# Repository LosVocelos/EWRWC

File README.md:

# EWRWC
Educational wheeled robot with camera

## Sources

These are the components (and their 3D models) I'm using in this project:

### Modules

| Part | Component | Store page | 3D model |
| ---------- | ---------- | ---------- | ---------- |
| EWRWC Add-on | Custom PCB (described below) | *None yet* | [Pi_zero_header.step](PCB/Pi_zero_header.step)
| Brain (CPU) | Raspberry pi zero 2 w | [RPishop - Zero 2 w](https://rpishop.cz/zero/4311-raspberry-pi-zero-2-w-5056561800004.html) | [GrabCAD - Zero 2 w](https://grabcad.com/library/raspberry-pi-zero-2-w-1) |
| Camera | Raspberry Pi camera V2 | [RPishop - camera v2](https://rpishop.cz/mipi-kamerove-moduly/329-raspberry-pi-kamera-modul-v2.html) | [Thingiverse - Rpi Camera v2.1](https://www.thingiverse.com/thing:2376448/files) |
| Camera cable (200 mm) | Camera Cable Standard - Mini | [RPishop - camera cable](https://rpishop.cz/mipi-kamerove-moduly/329-raspberry-pi-kamera-modul-v2.html) |  |
| 2x DC motor | 2x GA12-N20 3V 500RPM | [Techfun - motor 3V 500RPM](https://techfun.sk/produkt/dc-motorcek-s-prevodom-rozne-typy/?attribute_pa_motor=3v-500rpm) | [GrabCAD - N20 Gearmotor](https://grabcad.com/library/dc-micro-metal-gearmotor-1) |
| Ball (support point) | Rotating ball 3PI N20 | [Techfun - 3PI N20](https://techfun.sk/produkt/gulicka-n20-pre-stavebnice-robotickych-auticok/) |  |
| Battery holder | 18650 Li-Ion Holder | [LaskaKit - 18650 Holder](https://www.laskakit.cz/bateriovy-box-1x18650-dratove-vyvody/) | [GrabCAD - 18650 Holder](https://grabcad.com/library/18650-battery-holder-generic-1) |
| Battery | 18650 Li-Ion 2800mAh 10A | [Techfun - INR18650-28HE](https://techfun.sk/produkt/18650-bateria-tenpower-inr18650-28he-2800mah-10a/) |  |

*These components are optional, but I have examples for them:*

| Part | Component | Store page | 3D model |
| ---------- | ---------- | ---------- | ---------- |
| 3 axis Magnetometer | I2C HMC5883l | [LaskaKit - HMC5883l](https://www.laskakit.cz/3-osy-magnetometr-a-kompas-hmc5883l/) |  |
| Laser distance sensor | I2C VL53L0X | [LaskaKit - VL53L0X](https://www.laskakit.cz/laserovy-senzor-vzdalenosti-gy-vl53l0x-i2c/) |  |
| Module of light intensity | I2C GY-302 BH1750 | [RPishop - GY-302](https://rpishop.cz/svetlo/2435-modul-intenzity-svetla-gy-302-bh1750.html) |  |

*These components are optional, but I don't use them:*

| Part | Component | Store page | 3D model |
| ---------- | ---------- | ---------- | ---------- |
| Light intensity sensor | I2C VELM7700 | [LaskaKit - VELM7700](https://www.laskakit.cz/snimac-intenzity-osvetleni-veml7700--i2c/) |  |
| Temp + humidity sensor | I2C SHT30 | [LaskaKit - SHT30](https://www.laskakit.cz/senzor-teploty-a-vlhkosti-vzduchu-sht30/) |  |
| Blue + Yellow OLED | SPI OLED 128x64 | [LaskaKit - OLED 0.96"](https://www.laskakit.cz/oled-displej-modry-a-zluty-128x64-0-96--spi/) |  |
| Blue + Yellow OLED | I2C OLED 128x64 | [LaskaKit - OLED 0.96"](https://www.laskakit.cz/oled-displej-modry-a-zluty-128x64-0-96--i2c/) |  |

### PCB (EWRWC Add-on)

I previously called the board a Pi-Zero-Header (that's why the files are called that way).
But that name didn't grasp the functionality well, so I decided to call it EWRWC Add-on (I wanted to call it the HAT, but by board doesn't meet all requirements to be called that way).

List of parts used in the Add-on board:

| Part | Manufacturer | Component | Store page | Documentation |
| ---------- | ---------- | ---------- | ---------- | ---------- |
| Microcontroller | Raspberry Pi | RP2040 | [LCSC - RP2040](https://www.lcsc.com/product-detail/Microcontroller-Units-MCUs-MPUs-SOCs_Raspberry-Pi-RP2040_C2040.html) | [rp2040-datasheet.pdf](https://datasheets.raspberrypi.com/rp2040/rp2040-datasheet.pdf) |
| MCU Flash memory | Winbond | Q25W128JV | [JLCPCB - Q25W128JVSIQ](https://jlcpcb.com/partdetail/WinbondElec-W25Q128JVSIQ/C97521) | [W25Q128JV.pdf](https://www.winbond.com/resource-files/W25Q128JV%20RevI%2008232021%20Plus.pdf) |
| MCU Crystal | YXC | X322512MSB4SI | [JLCPCB - X322512MSB4SI](https://jlcpcb.com/partdetail/Yxc-X322512MSB4SI/C9002) | [YSX321SL.pdf](https://image.seapx.com/mall/yangxin/3/20231030/YSX321SL-687795.pdf) |
| Battery management | Texas Instruments | BQ25792 | [LCSC - BQ25792](https://www.lcsc.com/product-detail/Battery-Management-ICs_Texas-Instruments-BQ25792RQMR_C2862876.html) | [bq25792.pdf](https://www.ti.com/lit/ds/symlink/bq25792.pdf) |
| 5V / 3V3 Regulator | Texas Instruments | TPS63070 | [LCSC - TPS63070](https://www.lcsc.com/product-detail/DC-DC-Converters_Texas-Instruments-TPS63070RNMR_C109322.html) | [tps63070.pdf](https://www.ti.com/lit/ds/symlink/tps63070.pdf) |
| 5V / 3V3 Regulator | Chilisin Elec | BMRA000404201R0MA1 | [LCSC - BMRA000404201R0](https://www.lcsc.com/product-detail/Power-Inductors_Chilisin-Elec-BMRA000404201R0MA1_C2838337.html) | [BMRx_Series.pdf](https://www.chilisin.com/upload/media/product/power/file/BMRx_Series.pdf) |
| Motor Driver (2 H) | Toshiba | TB6612FNG | [LCSC - TB6612FNG](https://www.lcsc.com/product-detail/Motor-Driver-ICs_TOSHIBA-TB6612FNG-O-C-8-EL_C88224.html) | [TB6612FNG.pdf](https://toshiba.semicon-storage.com/info/TB6612FNG_datasheet_en_20141001.pdf?did=10660&prodName=TB6612FNG) |

There are much more parts used in this project (inductors, buttons, connectors, LEDs and a bunch of capacitors and resistors), but only those in the table are crucialfor the functionality and choosing the rest of the parts.

--------------------------------------------------

TODO:

- [x] Gather all sources
- [x] Design the main PCB
- [x] Complete the PCB
- [x] Design chassis
- [x] Print and ready the chassis
- [x] Complete the hardware
- [x] Write the software
- [x] Write the framework
- [x] Add some use for the camera
- [x] Write documentation
- [ ] Finalize
- [ ] Play with it :)

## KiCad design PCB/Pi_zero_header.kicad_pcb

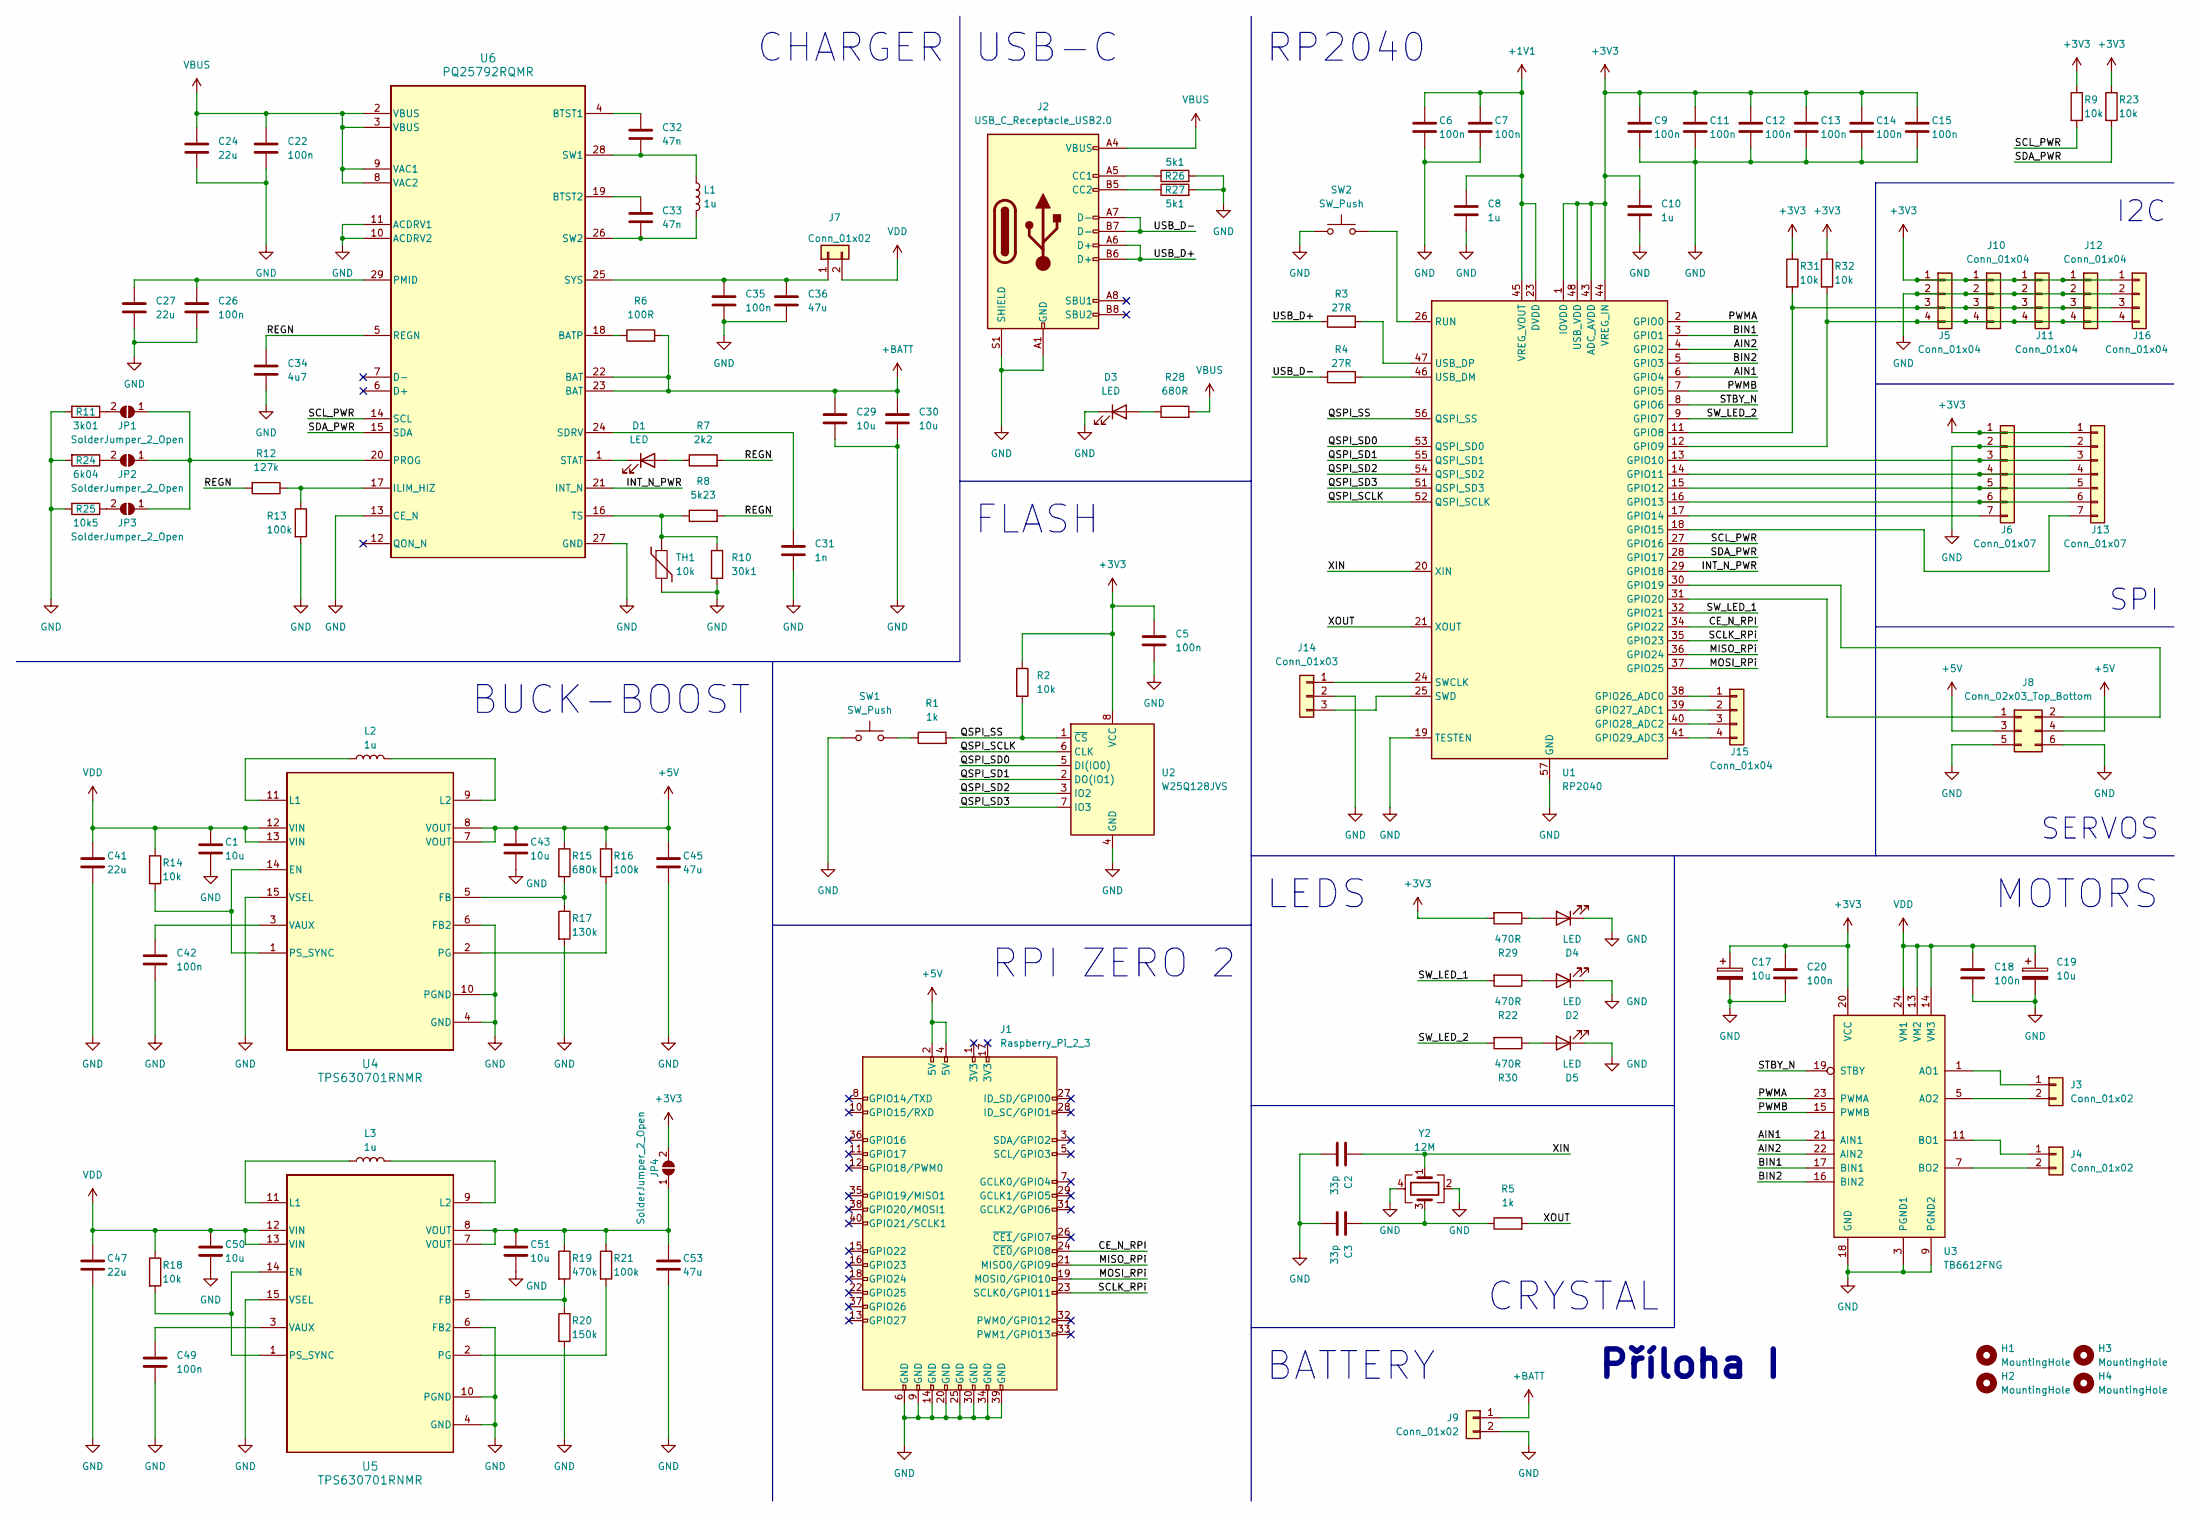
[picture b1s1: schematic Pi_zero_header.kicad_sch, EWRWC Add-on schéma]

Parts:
C1, C43, C50, C51: 10u; C_0603_1608Metric; LCSC C96446
C2, C3: 33p; C_0402_1005Metric; LCSC C1562
C5, C6, C7, C9, C11, C12, C13, C14, C15: 100n; C_0402_1005Metric; LCSC C1525
C8, C10: 1u; C_0402_1005Metric; LCSC C52923
C17, C19: 10u; CP_EIA-3216-18_Kemet-A; LCSC C7171
C18, C20, C22, C26, C35, C42, C49: 100n; C_0402_1005Metric; LCSC C307331
C24, C27, C41, C47: 22u; C_0805_2012Metric; LCSC C45783
C29, C30: 10u; C_0805_2012Metric; LCSC C440198
C31: 1n; C_0402_1005Metric; LCSC C1523
C32, C33: 47n; C_0402_1005Metric; LCSC C307339
C34: 4u7; C_0603_1608Metric; LCSC C19666
C36: 47u; C_1206_3216Metric; LCSC C96123
C45, C53: 47u; C_0805_2012Metric; LCSC C16780
D1, D2: LED; LED_0603_1608Metric; LCSC C2286
D3, D4: LED; LED_0805_2012Metric; LCSC C2297
D5: LED; LED_0603_1608Metric; LCSC C72038
H1, H2, H3, H4: MountingHole; MountingHole_2.7mm
J1: Raspberry_Pi_2_3; PinSocket_2x20_P2.54mm_Vertical; LCSC C5307344
J2: USB_C_Receptacle_USB2.0; USB_C_Receptacle_HCTL_HC-TYPE-C-16P-01A; LCSC C2894897
J3, J4, J7, J9: Conn_01x02; PinHeader_1x02_P2.54mm_Vertical
J5, J10, J11, J12, J15, J16: Conn_01x04; PinHeader_1x04_P1.27mm_Vertical
J6, J13: Conn_01x07; PinHeader_1x07_P1.27mm_Vertical
J8: Conn_02x03_Top_Bottom; PinHeader_2x03_P2.54mm_Vertical
J14: Conn_01x03; PinHeader_1x03_P1.27mm_Vertical
JP1, JP2, JP3, JP4: SolderJumper_2_Open; SolderJumper-2_P1.3mm_Open_RoundedPad1.0x1.5mm
L1, L2, L3: 1u; L_Chilisin_BMRA00040420; LCSC C2838337
R1, R5: 1k; R_0402_1005Metric; LCSC C11702
R2, R9, R14, R18, R23, R31, R32: 10k; R_0402_1005Metric; LCSC C25744
R3, R4: 27R; R_0402_1005Metric; LCSC C25100
R6: 100R; R_0402_1005Metric; LCSC C25076
R7: 2k2; R_0402_1005Metric; LCSC C25879
R8: 5k23; R_0402_1005Metric; LCSC C25907
R10: 30k1; R_0402_1005Metric; LCSC C29402
R11: 3k01; R_0402_1005Metric; LCSC C25889
R12: 127k; R_0402_1005Metric; LCSC C25751
R13, R16, R21: 100k; R_0402_1005Metric; LCSC C25741
R15: 680k; R_0402_1005Metric; LCSC C4131
R17: 130k; R_0402_1005Metric; LCSC C52929
R19: 470k; R_0402_1005Metric; LCSC C25790
R20: 150k; R_0402_1005Metric; LCSC C25755
R22, R29, R30: 470R; R_0402_1005Metric; LCSC C25117
R24: 6k04; R_0402_1005Metric; LCSC C25913
R25: 10k5; R_0402_1005Metric; LCSC C25850
R26, R27: 5k1; R_0402_1005Metric; LCSC C25905
R28: 680R; R_0402_1005Metric; LCSC C25130
SW1, SW2: SW_Push; SW_SPST_PTS810; LCSC C116501
TH1: 10k; R_Axial_DIN0204_L3.6mm_D1.6mm_P2.54mm_Vertical
U1: RP2040; QFN-56-1EP_7x7mm_P0.4mm_EP3.2x3.2mm; LCSC C2040
U2: W25Q128JVS; SOIC-8_5.23x5.23mm_P1.27mm; LCSC C97521
U3: TB6612FNG; SSOP-24_5.3x8.2mm_P0.65mm; LCSC C88224
U4, U5: TPS630701RNMR; RNM0015A; LCSC C109322
U6: PQ25792RQMR; RQM0029A-MFG; LCSC C2862876
Y2: 12M; Crystal_SMD_3225-4Pin_3.2x2.5mm; LCSC C9002

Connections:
+1V1: C6.1, C7.1, C8.1, U1.23 (DVDD), U1.45 (VREG_VOUT), U1.50 (DVDD)
+3V3: C5.1, C9.1, C10.1, C11.1, C12.1, C13.1, C14.1, C15.1, C17.1, C20.1, J5.1, J6.1, J10.1, J11.1, J12.1, J13.1, J16.1, JP4.2 (B), R2.1, R9.1, R23.1, R29.2, R31.1, R32.1, U1.1 (IOVDD), U1.10 (IOVDD), U1.22 (IOVDD), U1.33 (IOVDD), U1.42 (IOVDD), U1.43 (ADC_AVDD), U1.44 (VREG_IN), U1.48 (USB_VDD), U1.49 (IOVDD), U2.8 (VCC), U3.20 (VCC)
+5V: C43.1, C45.1, J1.2 (5V), J1.4 (5V), J8.3, J8.4, R15.1, R16.1, U4.7 (VOUT), U4.8 (VOUT)
+BATT: C29.1, C30.1, J9.1, R6.2, U6.22 (BAT), U6.23 (BAT)
/AIN1: U1.6 (GPIO4), U3.21 (AIN1)
/AIN2: U1.4 (GPIO2), U3.22 (AIN2)
/BIN1: U1.3 (GPIO1), U3.17 (BIN1)
/BIN2: U1.5 (GPIO3), U3.16 (BIN2)
/CE_N_RPI: J1.24 (~CE0/GPIO8), U1.34 (GPIO22)
/INT_N_PWR: U1.29 (GPIO18), U6.21 (INT_N)
/MISO_RPi: J1.21 (MISO0/GPIO9), U1.36 (GPIO24)
/MOSI_RPi: J1.19 (MOSI0/GPIO10), U1.37 (GPIO25)
/PWMA: U1.2 (GPIO0), U3.23 (PWMA)
/PWMB: U1.7 (GPIO5), U3.15 (PWMB)
/QSPI_SCLK: U1.52 (QSPI_SCLK), U2.6 (CLK)
/QSPI_SD0: U1.53 (QSPI_SD0), U2.5 (DI(IO0))
/QSPI_SD1: U1.55 (QSPI_SD1), U2.2 (DO(IO1))
/QSPI_SD2: U1.54 (QSPI_SD2), U2.3 (IO2)
/QSPI_SD3: U1.51 (QSPI_SD3), U2.7 (IO3)
/QSPI_SS: R1.2, R2.2, U1.56 (QSPI_SS), U2.1 (~CS)
/REGN: C34.1, R7.2, R8.2, R12.2, U6.5 (REGN)
/SCLK_RPi: J1.23 (SCLK0/GPIO11), U1.35 (GPIO23)
/SCL_PWR: R9.2, U1.27 (GPIO16), U6.14 (SCL)
/SDA_PWR: R23.2, U1.28 (GPIO17), U6.15 (SDA)
/STBY_N: U1.8 (GPIO6), U3.19 (STBY)
/SW_LED_1: R22.2, U1.32 (GPIO21)
/SW_LED_2: R30.2, U1.9 (GPIO7)
/USB_D+: J2.A6 (D+), J2.B6 (D+), R3.1
/USB_D-: J2.A7 (D-), J2.B7 (D-), R4.1
/XIN: C2.1, U1.20 (XIN), Y2.1
/XOUT: R5.2, U1.21 (XOUT)
GND: C1.2, C2.2, C3.2, C5.2, C6.2, C7.2, C8.2, C9.2, C10.2, C11.2, C12.2, C13.2, C14.2, C15.2, C17.2, C18.2, C19.2, C20.2, C22.2, C24.2, C26.2, C27.2, C29.2, C30.2, C31.2, C34.2, C35.2, C36.2, C41.2, C42.2, C43.2, C45.2, C47.2, C49.2, C50.2, C51.2, C53.2, D2.1 (K), D3.1 (K), D4.1 (K), D5.1 (K), J1.6 (GND), J1.9 (GND), J1.14 (GND), J1.20 (GND), J1.25 (GND), J1.30 (GND), J1.34 (GND), J1.39 (GND), J2.A1 (GND), J2.A12 (GND), J2.B1 (GND), J2.B12 (GND), J2.S1 (SHIELD), J5.2, J6.2, J8.5, J8.6, J9.2, J10.2, J11.2, J12.2, J13.2, J14.2, J16.2, R10.2, R11.2, R13.2, R17.2, R20.2, R24.2, R25.2, R26.2, R27.2, SW1.1, SW2.1, TH1.2, U1.19 (TESTEN), U1.57 (GND), U2.4 (GND), U3.3 (PGND1), U3.4 (PGND1), U3.9 (PGND2), U3.10 (PGND2), U3.18 (GND), U4.4 (GND), U4.6 (FB2), U4.10 (PGND), U4.15 (VSEL), U5.4 (GND), U5.6 (FB2), U5.10 (PGND), U5.15 (VSEL), U6.10 (ACDRV2), U6.11 (ACDRV1), U6.13 (CE_N), U6.27 (GND), Y2.2, Y2.4
unnamed: C3.1, R5.1, Y2.3
unnamed: D1.2 (A), R7.1
unnamed: D1.1 (K), U6.1 (STAT)
unnamed: D2.2 (A), R22.1
unnamed: D3.2 (A), R28.1
unnamed: D4.2 (A), R29.1
unnamed: D5.2 (A), R30.1
unnamed: J2.A5 (CC1), R26.1
unnamed: J2.B5 (CC2), R27.1
unnamed: J3.1, U3.1 (AO1), U3.2 (AO1)
unnamed: J3.2, U3.5 (AO2), U3.6 (AO2)
unnamed: J4.1, U3.11 (BO1), U3.12 (BO1)
unnamed: J4.2, U3.7 (BO2), U3.8 (BO2)
unnamed: J6.7, U1.17 (GPIO14)
unnamed: C35.1, C36.1, J7.1, U6.25 (SYS)
unnamed: J8.1, U1.31 (GPIO20)
unnamed: J8.2, U1.30 (GPIO19)
unnamed: J5.3, J10.3, J11.3, J12.3, J16.3, R31.2, U1.11 (GPIO8)
unnamed: J5.4, J10.4, J11.4, J12.4, J16.4, R32.2, U1.12 (GPIO9)
unnamed: J6.3, J13.3, U1.13 (GPIO10)
unnamed: J6.4, J13.4, U1.14 (GPIO11)
unnamed: J6.5, J13.5, U1.15 (GPIO12)
unnamed: J6.6, J13.6, U1.16 (GPIO13)
unnamed: J13.7, U1.18 (GPIO15)
unnamed: J14.1, U1.24 (SWCLK)
unnamed: J14.3, U1.25 (SWD)
unnamed: J15.1, U1.38 (GPIO26_ADC0)
unnamed: J15.2, U1.39 (GPIO27_ADC1)
unnamed: J15.3, U1.40 (GPIO28_ADC2)
unnamed: J15.4, U1.41 (GPIO29_ADC3)
unnamed: JP1.1 (A), JP2.1 (A), JP3.1 (A), U6.20 (PROG)
unnamed: JP1.2 (B), R11.1
unnamed: JP2.2 (B), R24.1
unnamed: JP3.2 (B), R25.1
unnamed: C51.1, C53.1, JP4.1 (A), R19.1, R21.1, U5.7 (VOUT), U5.8 (VOUT)
unnamed: R1.1, SW1.2
unnamed: SW2.2, U1.26 (RUN)
unnamed: R4.2, U1.46 (USB_DM)
unnamed: R3.2, U1.47 (USB_DP)
unnamed: R14.2, U4.1 (PS_SYNC), U4.14 (EN)
unnamed: R15.2, R17.1, U4.5 (FB)
unnamed: L2.1, U4.11 (L1)
unnamed: L2.2, U4.9 (L2)
unnamed: R16.2, U4.2 (PG)
unnamed: C42.1, U4.3 (VAUX)
unnamed: R18.2, U5.1 (PS_SYNC), U5.14 (EN)
unnamed: R19.2, R20.1, U5.5 (FB)
unnamed: L3.1, U5.11 (L1)
unnamed: L3.2, U5.9 (L2)
unnamed: R21.2, U5.2 (PG)
unnamed: C49.1, U5.3 (VAUX)
unnamed: R6.1, U6.18 (BATP)
unnamed: C32.1, U6.4 (BTST1)
unnamed: C33.1, U6.19 (BTST2)
unnamed: R12.1, R13.1, U6.17 (ILIM_HIZ)
unnamed: C26.1, C27.1, U6.29 (PMID)
unnamed: C31.1, U6.24 (SDRV)
unnamed: C32.2, L1.1, U6.28 (SW1)
unnamed: C33.2, L1.2, U6.26 (SW2)
unnamed: R8.1, R10.1, TH1.1, U6.16 (TS)
VBUS: C22.1, C24.1, J2.A4 (VBUS), J2.A9 (VBUS), J2.B4 (VBUS), J2.B9 (VBUS), R28.2, U6.2 (VBUS), U6.3 (VBUS), U6.8 (VAC2), U6.9 (VAC1)
VDD: C1.1, C18.1, C19.1, C41.1, C47.1, C50.1, J7.2, R14.1, R18.1, U3.13 (VM2), U3.14 (VM3), U3.24 (VM1), U4.12 (VIN), U4.13 (VIN), U5.12 (VIN), U5.13 (VIN)

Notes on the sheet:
LEDS
RP2040
BUCK-BOOST
BATTERY
I2C
CRYSTAL
SERVOS
USB-C
RPI ZERO 2
FLASH
MOTORS
Příloha I
CHARGER
SPI

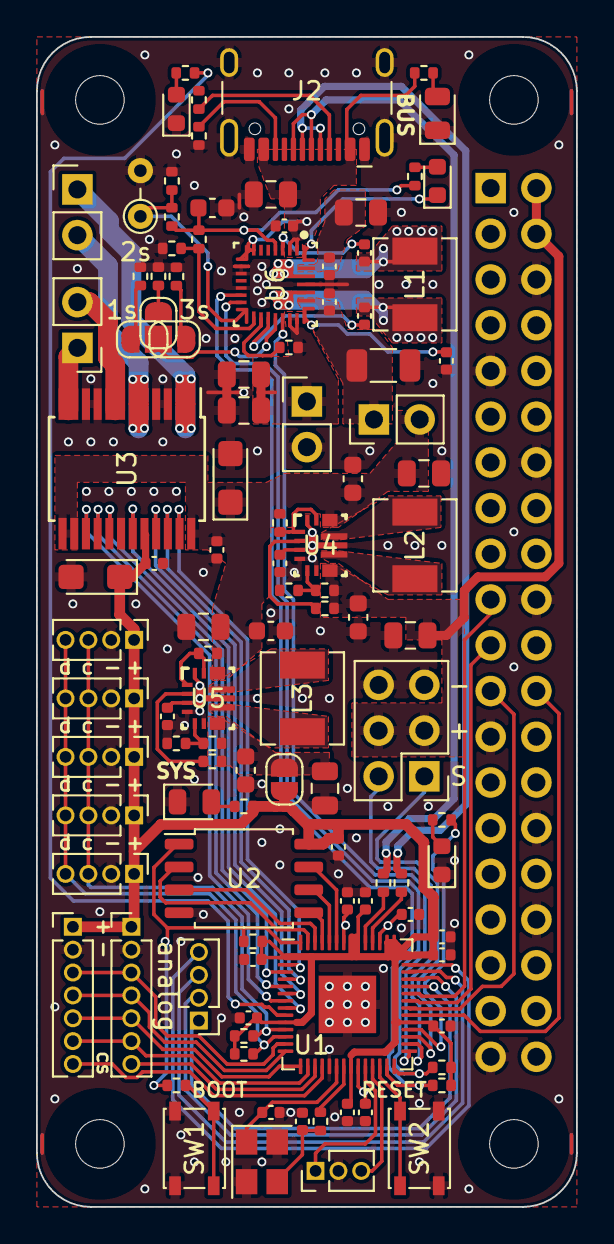
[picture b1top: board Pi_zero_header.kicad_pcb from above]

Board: 2 copper layers, 30.0 x 65.0 mm, 113 parts (1 on the bottom side), 94 nets.

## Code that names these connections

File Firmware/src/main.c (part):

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
#define STBY 6

const uint8_t motor_pins[] = {4, 2, 1, 3}; // AIN1, AIN2, BIN1, BIN2
const uint8_t pwm_pins[] = {0, 5, 19, 20}; // PWMA, PWMB, SERVOA, SERVOB

#define PWM_CLOCK_DIVIDE 25.f // Divide the PWM clock down to a more reasonable 1MHz to even be able to do 100hz but retain precision.
#define WRAP 49999.f // calculated so it matches 100hz (original frequency/desired frequency) - 1
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
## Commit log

2023-12-02 Moved PCB from another repo
2023-12-12 Updated and added TI charger
2023-12-12 Moved added parts to corretc folders
2023-12-12 Changed PCB design
2023-12-13 Update of PCB
2023-12-13 Edited schema
2023-12-15 Some changes
2023-12-19 Bruuuh...
2023-12-29 Added buck-boost converter to schema
2023-12-30 Added second buck-boost converter
2024-01-02 Hopefully done schema
2024-01-07 Added footprints
2024-01-09 I relized I fucked up...
2024-01-09 Idk what changed...
2024-01-11 Updated PCB design
2024-01-11 I will need different buck-boost...
2024-01-12 Another changes
2024-01-12 Another changes...
2024-01-13 Bruuuhhhh...
2024-01-13 Finally picked inductors
2024-01-14 Another changes to PCB
2024-01-14 Bruuuuh, me mad...
2024-01-14 Getting somewhere...
2024-01-14 Another commit :)
2024-01-15 Bruh, I forgor...
2024-01-15 Still working on PCB...
2024-01-16 Finally gonna rout'em
2024-01-16 Lolik...
2024-01-16 Finnaly routing
2024-01-17 Changed connectors
2024-01-18 Making changes...
2024-01-18 Aaaaaahhhh...
2024-01-22 Small changes
2024-01-25 Man! I don't like it anymore...
2024-01-26 Please! I wanna die!
2024-01-27 Bruh, I need to sleep...
2024-01-27 Added exact components to BOM
2024-01-27 Added a LED
2024-01-27 Ufff...
2024-01-27 Forgot about the inductors...
2024-01-28 Hehe, logos
2024-01-28 Repaired some shish...
2024-01-28 Yet another mistake.
2024-01-28 Added pull-ups
2024-01-28 Minor tweaks...
2024-01-28 Minor tweaks of silkscreen.
2024-01-28 Updated gerber
2024-01-28 Updated board
2024-01-28 Other tweaks
2024-02-01 Lolik
2024-02-02 Changed export tool and made some optimizations
2024-02-03 Hopefully final touches on PCB...
2024-02-03 Hopefully NOW final---
2024-02-04 Yes, I'm pushing at 4 AM...
2024-02-04 Added labels to buttons
2024-02-04 Generated 3D model
2024-02-09 Moved .gitignore
2024-02-12 Update README.md (small mistake with links)
2024-02-12 Just tweaking the silkscreen...
2024-02-13 Added docs (not complete)
2024-02-23 Testing i2c communication with BQ25792
2024-02-24 Typo in README.md
2024-02-28 Completely reworked firmware...
2024-02-28 Pushed the lib directory
2024-02-29 Added broken communication with BQ25792
2024-02-29 I AM IDIOT!
2024-02-29 Lolik pacholik
2024-03-01 It works! Kinda'...
2024-03-01 I was dumb, but now I am smart!
2024-03-02 Unga Bunga...
2024-03-03 Kind of yeeted the code together, but not the best way...
2024-03-15 Updated KiCAD
2024-03-16 Generated sheets
2024-03-16 Added few images to docs
2024-03-17 Another images...
2024-03-22 Yes, I know, this should be on LFS...
2024-03-25 Small graphics tweak
2024-03-25 Added software (not tested)
2024-03-26 Repair
2024-03-26 Debug print
2024-03-28 Working on the SPI slave
2024-03-29 A lot of Firmware changes
2024-03-29 Software tweaks
2024-03-31 Yeee, TOF sensor on first try!
2024-03-31 TOF broke... Idk why...
2024-03-31 Adding some printing to web
2024-03-31 Tweaks
2024-03-31 Why doesn't this sh*t work?!
2024-04-01 It kinda works now... Me sad...
2024-04-01 Added Blockly (not working yet)
2024-04-01 Repairt image output
2024-04-02 Added appendix files
2024-04-02 I'm dumb...
2024-04-03 Man... I need to make this video!
2024-04-05 Actually the most productive evening in a month...
2024-05-14 Implemented multicore on RP2040!
2025-03-11 Added blockly and jquery to .gitignore
2025-03-12 Added test.py for testing on PC
2025-03-13 Added python code generator
2025-03-13 Added zoom and custom blocks
2025-03-13 WIP Python editor and blockly to python conversion
2025-03-13 Fixed Python editor, still didn't add custom blocks
2025-03-14 Added toggle for Blovkly/Python editor

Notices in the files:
Firmware/src/main.c:
Copyright (c) 2021 Raspberry Pi (Trading) Ltd.
SPDX-License-Identifier: BSD-3-Clause
